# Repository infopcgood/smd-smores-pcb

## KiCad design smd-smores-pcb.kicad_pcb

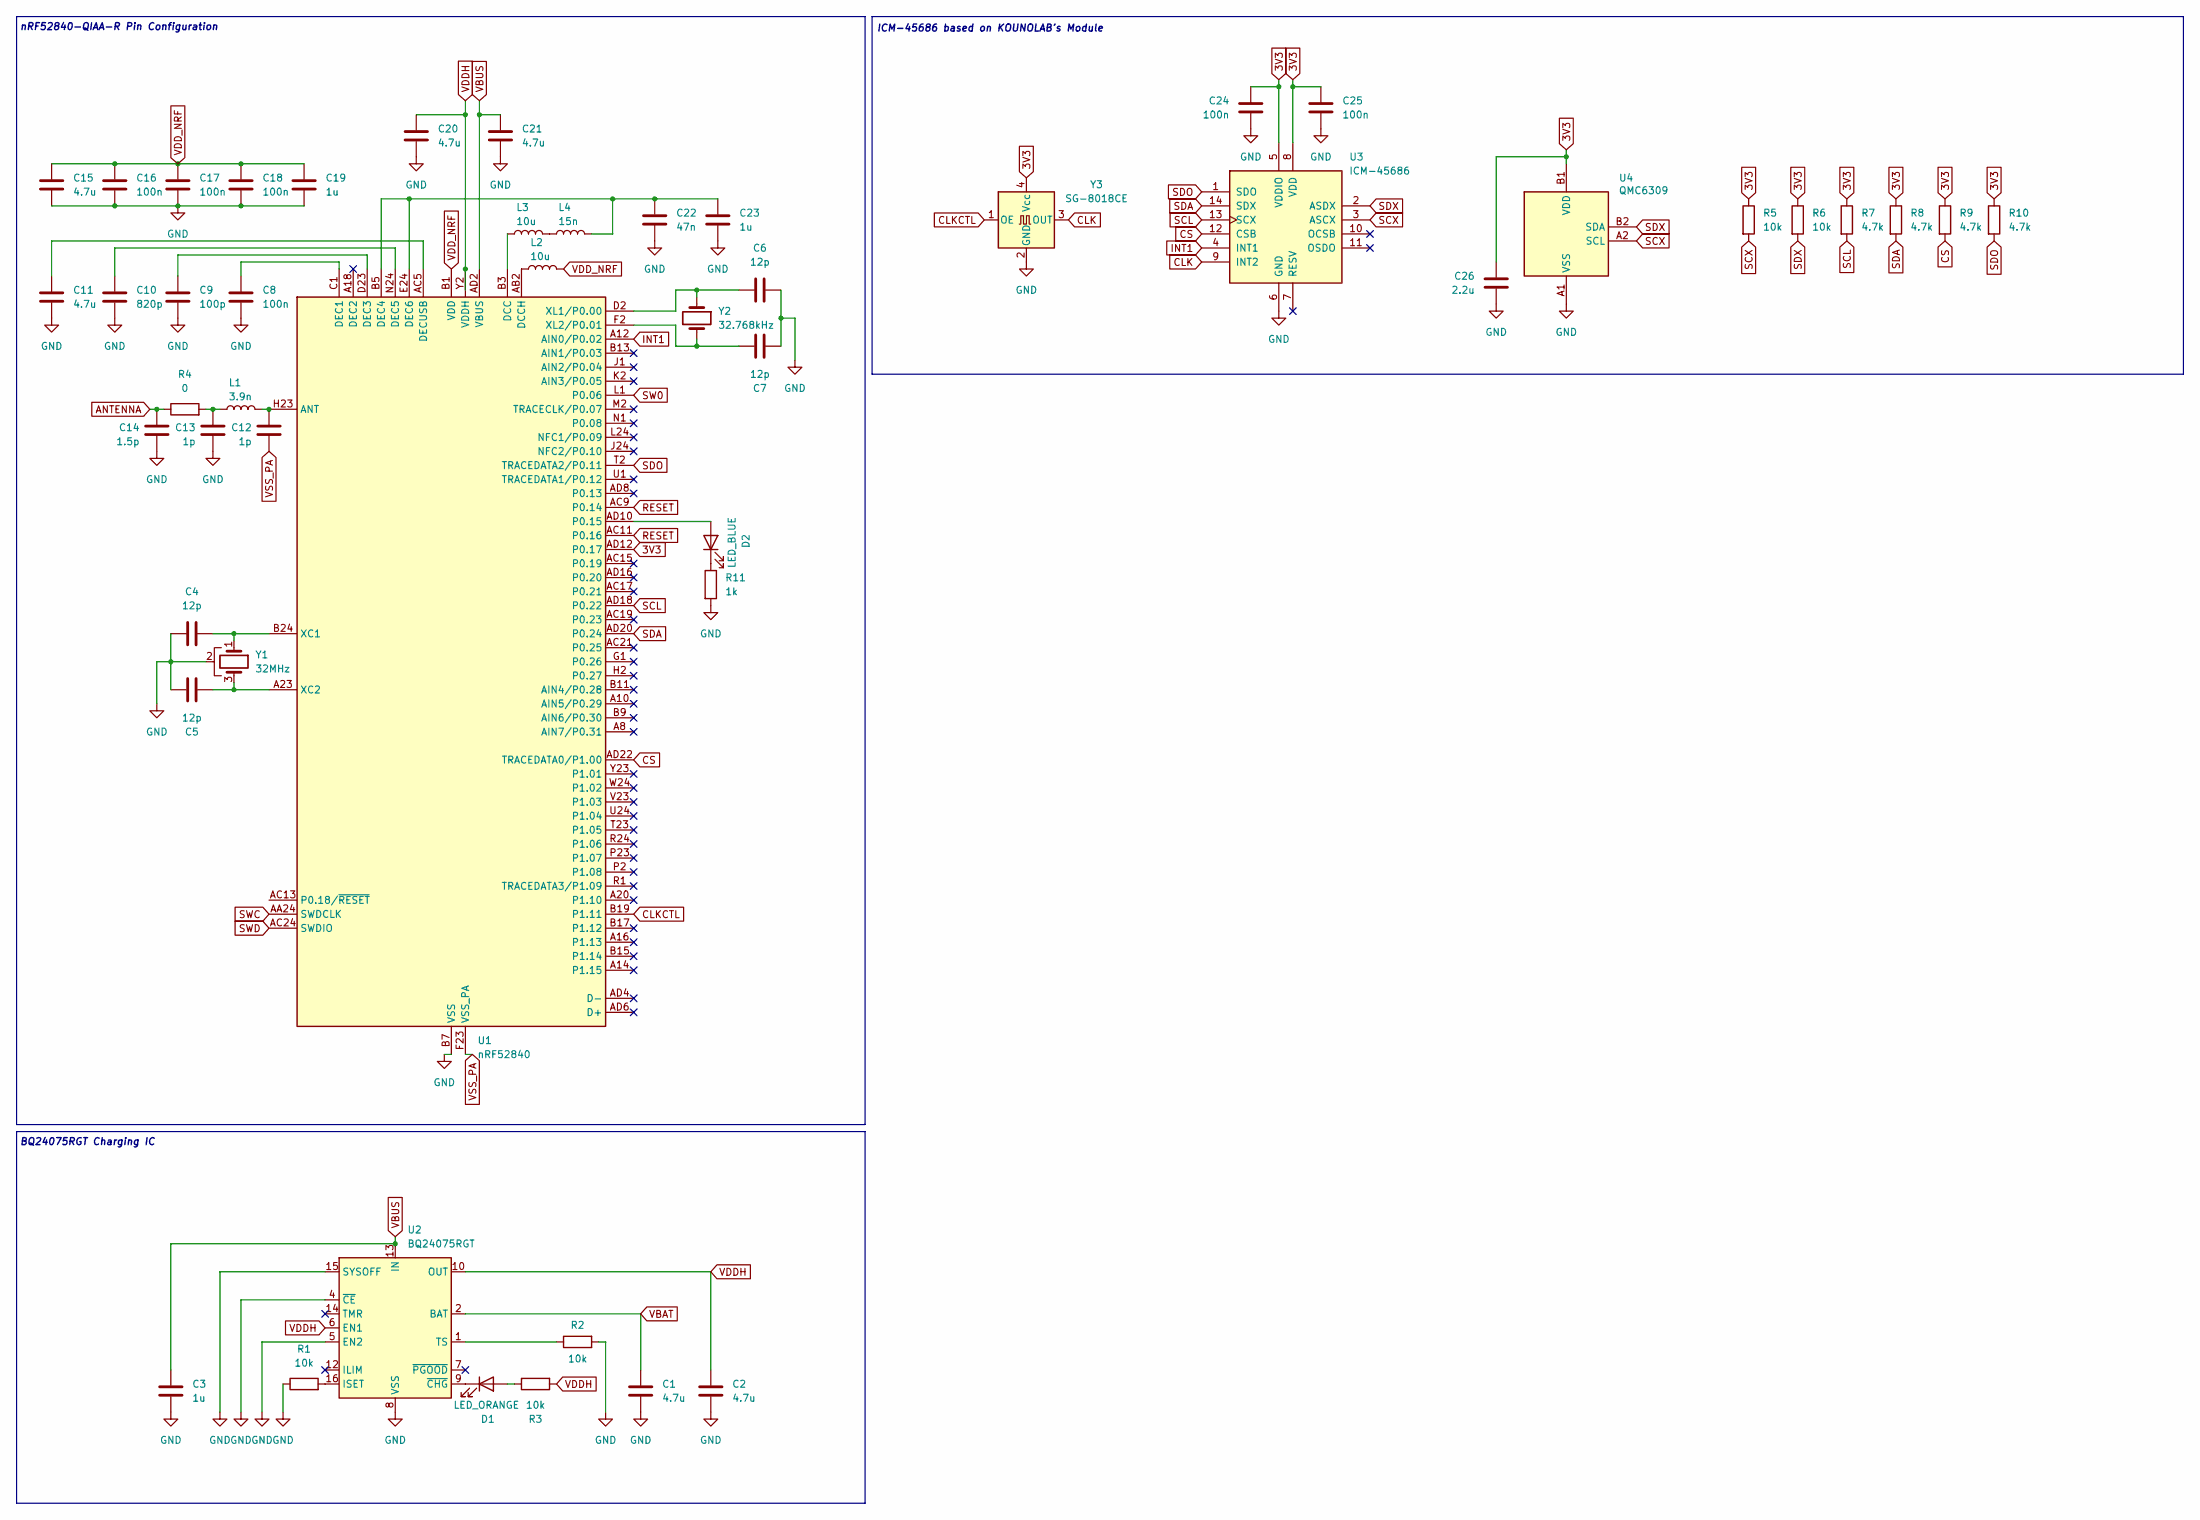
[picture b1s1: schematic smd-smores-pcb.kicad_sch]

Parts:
C1, C2, C11, C15, C20, C21: 4.7u; C_0402_1005Metric
C3, C19, C23: 1u; C_0402_1005Metric
C4, C5, C6, C7: 12p; C_0402_1005Metric
C8, C16, C17, C18, C24, C25: 100n; C_0402_1005Metric
C9: 100p; C_0402_1005Metric
C10: 820p; C_0402_1005Metric
C12, C13: 1p; C_0402_1005Metric
C14: 1.5p; C_0402_1005Metric
C22: 47n; C_0402_1005Metric
C26: 2.2u; C_0402_1005Metric
D1: LED_ORANGE; LED_0402_1005Metric
D2: LED_BLUE; LED_0402_1005Metric
L1: 3.9n; L_0402_1005Metric
L2, L3: 10u; L_0603_1608Metric
L4: 15n; L_0402_1005Metric
R1, R2, R3, R5, R6: 10k; R_0402_1005Metric
R4: 0; R_1206_3216Metric
R7, R8, R9, R10: 4.7k; R_0402_1005Metric
R11: 1k; R_0402_1005Metric
U1: nRF52840; Nordic_AQFN-73-1EP_7x7mm_P0.5mm
U2: BQ24075RGT; VQFN-16-1EP_3x3mm_P0.5mm_EP1.6x1.6mm
U3: ICM-45686; IC_ICM-45686; PARTREV 0.2
U4: QMC6309; IC_QMC6309
Y1: 32MHz; Crystal_SMD_3225-4Pin_3.2x2.5mm
Y2: 32.768kHz; Crystal_SMD_3215-2Pin_3.2x1.5mm
Y3: SG-8018CE; Oscillator_SMD_SeikoEpson_SG8002CE-4Pin_3.2x2.5mm

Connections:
3V3: C24.1, C25.1, C26.1, R5.1, R6.1, R7.1, R8.1, R9.1, R10.1, U1.AD12 (P0.17), U3.5 (VDDIO), U3.8 (VDD), U4.B1 (VDD), Y3.4 (Vcc)
ANTENNA: C14.1, R4.1
CLK: U3.9 (INT2), Y3.3 (OUT)
CLKCTL: U1.B19 (P1.11), Y3.1 (OE)
CS: R9.2, U1.AD22 (TRACEDATA0/P1.00), U3.12 (CSB)
GND: C1.2, C2.2, C3.2, C4.1, C5.1, C6.1, C7.1, C8.2, C9.2, C10.2, C11.2, C13.2, C14.2, C15.2, C16.2, C17.2, C18.2, C19.2, C20.2, C21.2, C22.2, C23.2, C24.2, C25.2, C26.2, R1.1, R2.2, R11.2, U1.B7 (VSS), U1.EP (VSS), U2.4 (~CE), U2.5 (EN2), U2.8 (VSS), U2.15 (SYSOFF), U2.17 (VSS), U3.6 (GND), U4.A1 (VSS), Y1.2, Y3.2 (GND)
INT1: U1.A12 (AIN0/P0.02), U3.4 (INT1)
unnamed: C13.1, L1.1, R4.2
unnamed: D1.2 (A), R3.1
unnamed: D1.1 (K), U2.9 (~CHG)
unnamed: D2.2 (A), U1.AD10 (P0.15)
unnamed: D2.1 (K), R11.1
unnamed: L3.2, L4.1
unnamed: C12.1, L1.2, U1.H23 (ANT)
unnamed: L3.1, U1.B3 (DCC)
unnamed: L2.1, U1.AB2 (DCCH)
unnamed: C8.1, U1.C1 (DEC1)
unnamed: C9.1, U1.D23 (DEC3)
unnamed: C22.1, C23.1, L4.2, U1.B5 (DEC4), U1.E24 (DEC6)
unnamed: C10.1, U1.N24 (DEC5)
unnamed: C11.1, U1.AC5 (DECUSB)
unnamed: C4.2, U1.B24 (XC1), Y1.1
unnamed: C5.2, U1.A23 (XC2), Y1.3
unnamed: C6.2, U1.D2 (XL1/P0.00), Y2.1
unnamed: C7.2, U1.F2 (XL2/P0.01), Y2.2
unnamed: R1.2, U2.16 (ISET)
unnamed: R2.1, U2.1 (TS)
RESET: U1.AC9 (P0.14), U1.AC11 (P0.16)
SCL: R7.2, U1.AD18 (P0.22), U3.13 (SCX)
SCX: R5.2, U3.3 (ASCX), U4.A2 (SCL)
SDA: R8.2, U1.AD20 (P0.24), U3.14 (SDX)
SDO: R10.2, U1.T2 (TRACEDATA2/P0.11), U3.1 (SDO)
SDX: R6.2, U3.2 (ASDX), U4.B2 (SDA)
SW0: U1.L1 (P0.06)
SWC: U1.AA24 (SWDCLK)
SWD: U1.AC24 (SWDIO)
VBAT: C1.1, U2.2 (BAT), U2.3 (BAT)
VBUS: C3.1, C21.1, U1.AD2 (VBUS), U2.13 (IN)
VDDH: C2.1, C20.1, R3.2, U1.Y2 (VDDH), U2.6 (EN1), U2.10 (OUT), U2.11 (OUT)
VDD_NRF: C15.1, C16.1, C17.1, C18.1, C19.1, L2.2, U1.A22 (VDD), U1.AD14 (VDD), U1.AD23 (VDD), U1.B1 (VDD), U1.W1 (VDD)
VSS_PA: C12.2, U1.F23 (VSS_PA)

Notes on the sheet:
nRF52840-QIAA-R Pin Configuration
ICM-45686 based on KOUNOLAB's Module
BQ24075RGT Charging IC

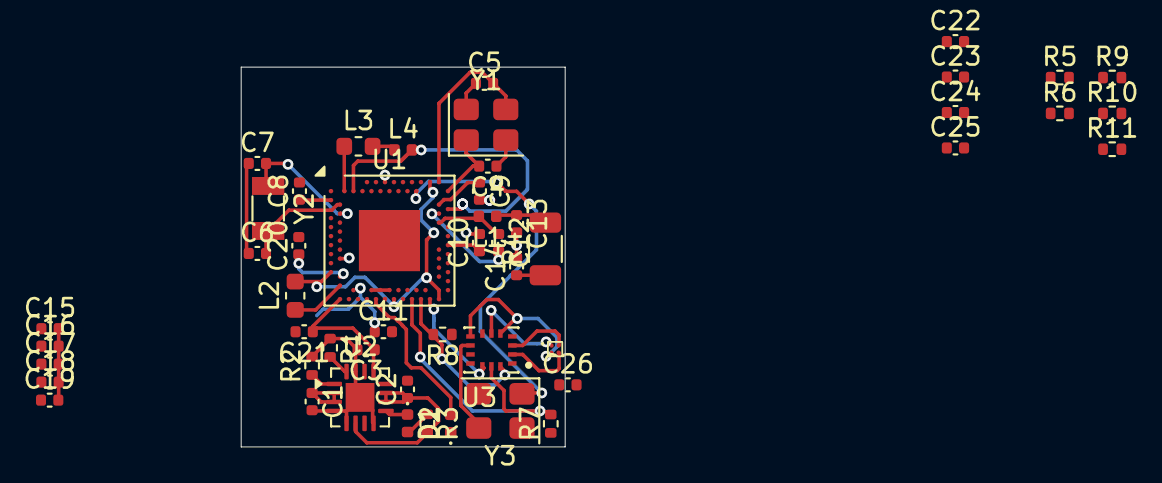
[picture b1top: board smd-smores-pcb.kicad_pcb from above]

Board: 2 copper layers, 18.0 x 21.1 mm, 50 parts (0 on the bottom side), 38 nets.

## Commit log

2025-11-30 Basic schematic design without peripherals
2025-11-30 Mid design v1
